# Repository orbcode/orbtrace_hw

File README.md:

ORBTrace Hardware
=================

This is the repository for various hardware for the ORBTrace project. There are various bits and pieces here but the most important ones are;

* ORBTrace Mini V1.0
* ORBMule demo board
* Breakout board for PMOD

You can also find the openSCAD source materials, and vinyl graphics, for the ORBTrace Mini V1 case.

These materials are provided in open form to learn from and improve on. We have deliberately chosen to not provide Gerbers for ORBTrace mini or STLs for the caseworks since your manufacturing processes are likely different to ours. Drop a note if you need those.

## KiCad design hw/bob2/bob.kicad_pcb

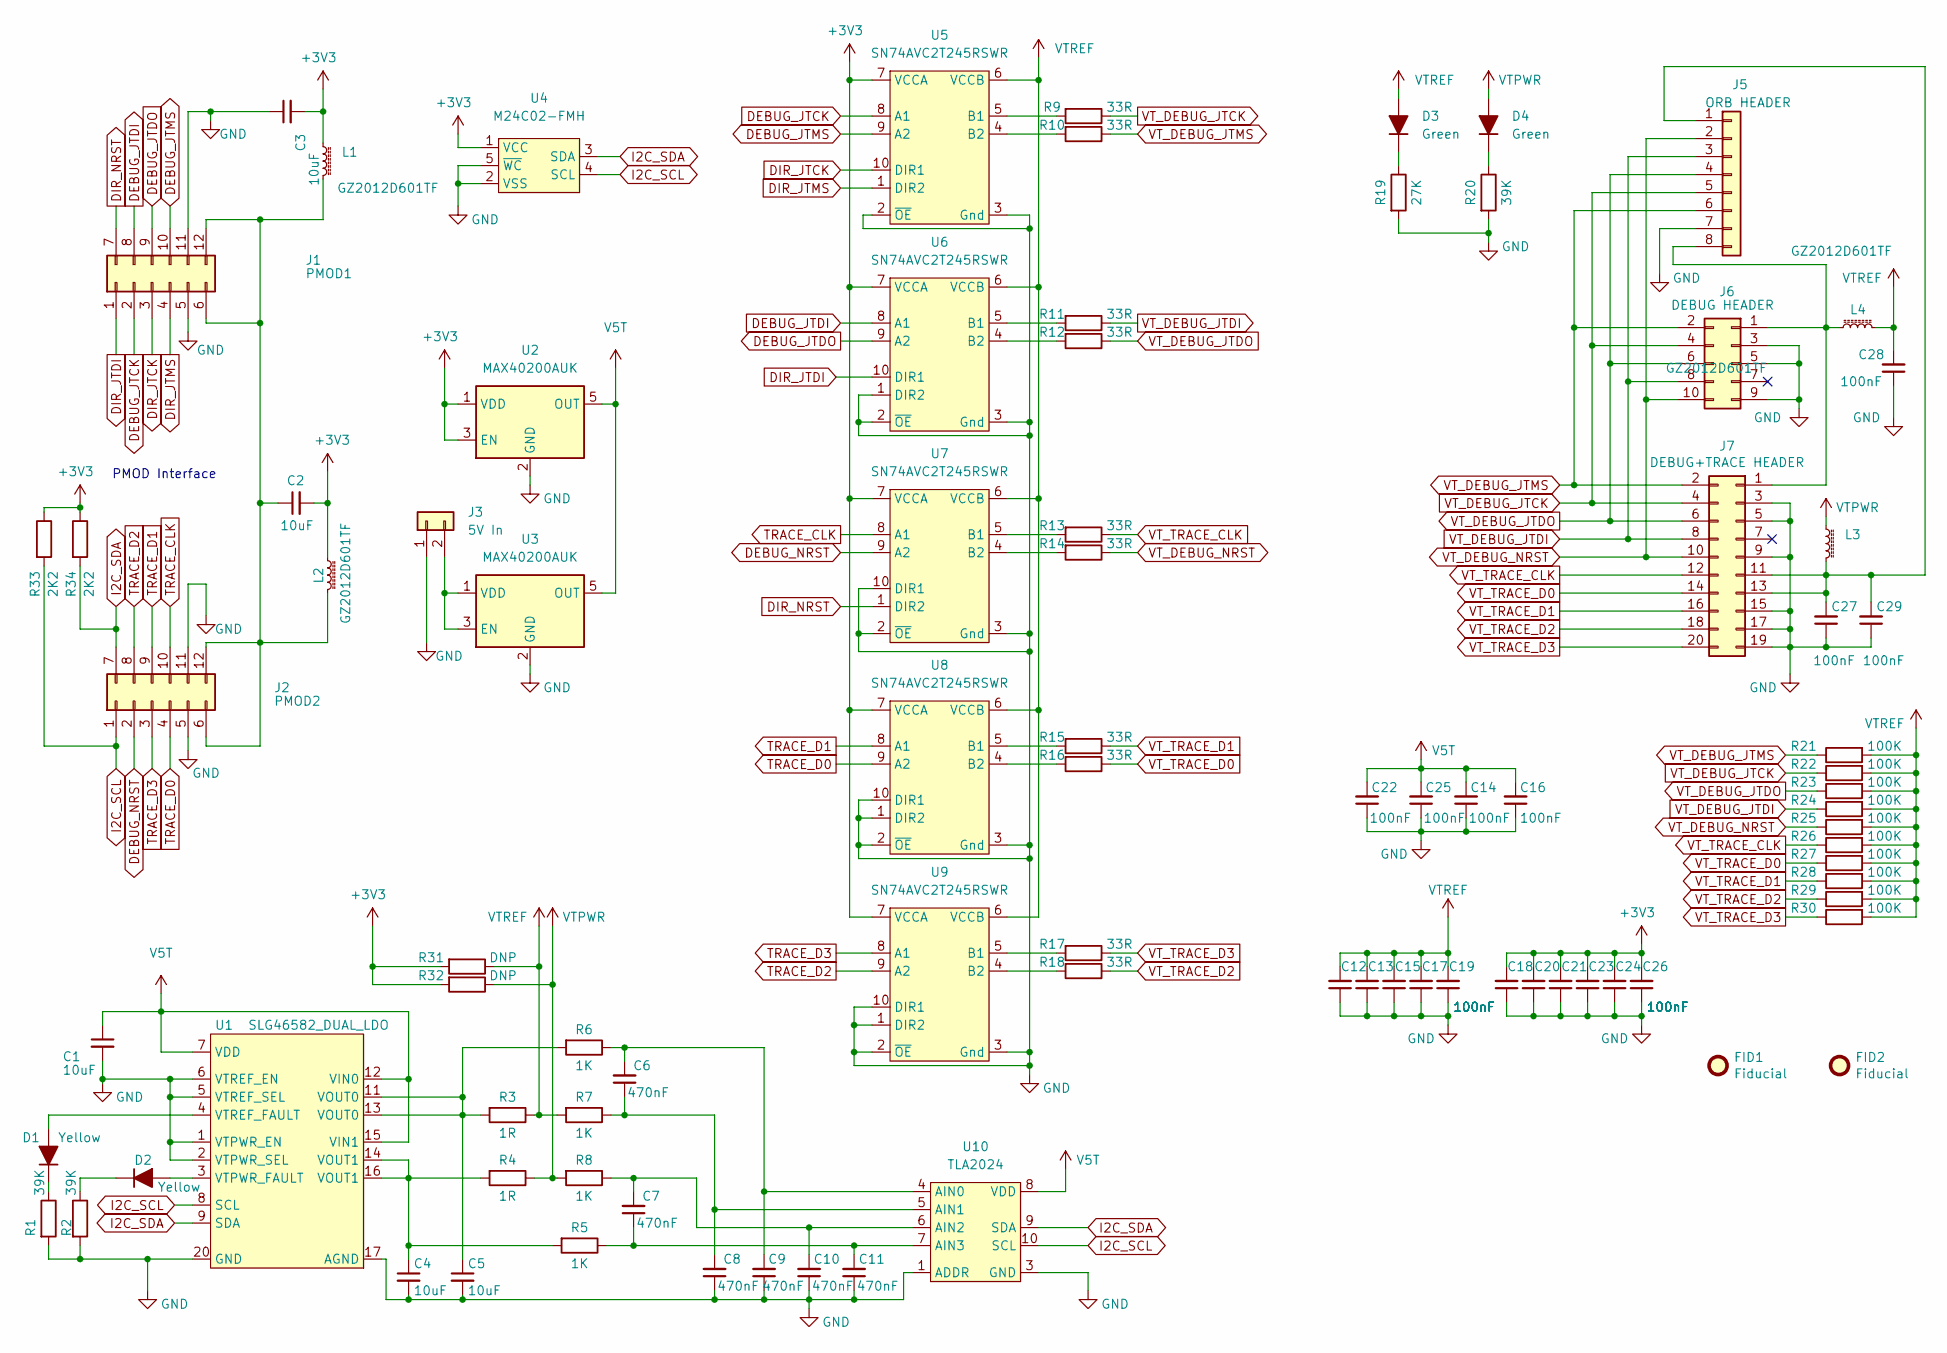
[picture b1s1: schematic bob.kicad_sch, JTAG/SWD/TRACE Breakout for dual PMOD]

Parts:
C1, C2, C3, C4, C5: 10uF; C_0603_1608Metric; JLC CODE C19702
C6, C7, C8, C9, C10, C11: 470nF; C_0402_1005Metric; JLC CODE C47339
C12, C13, C14, C15, C16, C17, C18, C19, C20, C21, C22, C23, C24, C25, C26, C27, C28, C29: 100nF; C_0402_1005Metric; JLC CODE C307331
D1, D2: Yellow; LED_0603_1608Metric; JLC CODE C72038
D3, D4: Green; LED_0603_1608Metric; JLC CODE C72043
FID1, FID2: Fiducial; Fiducial_0.75mm_Mask1.5mm
J1: PMOD1; pmod_pin_array_6x2
J2: PMOD2; pmod_pin_array_6x2
J3: 5V In; PinHeader_1x02_P2.54mm_Vertical
J5: ORB HEADER; PinHeader_1x08_P2.54mm_Vertical
J6: DEBUG HEADER; PinHeader_2x05_P1.27mm_Vertical_SMD
J7: DEBUG+TRACE HEADER; PinHeader_2x10_P1.27mm_Vertical_SMD
L1, L2, L3, L4: GZ2012D601TF; L_0805_2012Metric; JLC CODE C1017
R1, R2, R20: 39K; R_0402_1005Metric; JLC CODE C25783
R3, R4: 1R; R_0603_1608Metric; JLC CODE C22936
R5, R6, R7, R8: 1K; R_0402_1005Metric; JLC CODE C21190
R9, R10, R11, R12, R13, R14, R15, R16, R17, R18: 33R; R_0603_1608Metric; JLC CODE C23140
R19: 27K; R_0402_1005Metric; JLC CODE C25771
R21, R22, R23, R24, R25, R26, R27, R28, R29, R30: 100K; R_0402_1005Metric; JLC CODE C22936
R31, R32: DNP; R_0603_1608Metric
R33, R34: 2K2; R_0402_1005Metric; JLC CODE C4190
U1: SLG46582_DUAL_LDO; STQFN-20
U2, U3: MAX40200AUK; SOT-23-5; JLC CODE C2649430
U4: M24C02-FMH; DFN-5; JLC CODE C222197
U5, U6, U7, U8, U9: SN74AVC2T245RSWR; UQFN-10; JLC CODE C128418
U10: TLA2024; PQFP-N10; JLC CODE C2876104

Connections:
+3V3: C2.2, C3.2, C18.2, C20.2, C21.2, C23.2, C24.2, C26.2, L1.1, L2.1, R31.2, R32.2, R33.1, R34.1, U2.1 (VDD), U2.3 (EN), U4.1 (VCC), U5.7 (VCCA), U6.7 (VCCA), U7.7 (VCCA), U8.7 (VCCA), U9.7 (VCCA)
DEBUG_JTCK: J1.2, U5.8 (A1)
DEBUG_JTDI: J1.8, U6.8 (A1)
DEBUG_JTDO: J1.9, U6.9 (A2)
DEBUG_JTMS: J1.10, U5.9 (A2)
DEBUG_NRST: J2.2, U7.9 (A2)
DIR_JTCK: J1.3, U5.10 (DIR1)
DIR_JTDI: J1.1, U6.10 (DIR1)
DIR_JTMS: J1.4, U5.1 (DIR2)
DIR_NRST: J1.7, U7.1 (DIR2)
GND: C1.2, C3.1, C4.2, C5.2, C8.1, C9.1, C10.1, C11.1, C12.1, C13.1, C14.1, C15.1, C16.1, C17.1, C18.1, C19.1, C20.1, C21.1, C22.1, C23.1, C24.1, C25.1, C26.1, C27.1, C28.1, C29.1, J1.5, J1.11, J2.5, J2.11, J3.1, J5.7, J6.3, J6.5, J6.9, J7.3, J7.5, J7.9, J7.15, J7.17, J7.19, R1.2, R2.2, R19.2, R20.2, U1.1 (VTPWR_EN), U1.2 (VTPWR_SEL), U1.5 (VTREF_SEL), U1.6 (VTREF_EN), U1.17 (AGND), U1.20 (GND), U2.2 (GND), U3.2 (GND), U4.2 (VSS), U4.5 (~WC), U5.2 (~OE), U5.3 (Gnd), U6.1 (DIR2), U6.2 (~OE), U6.3 (Gnd), U7.2 (~OE), U7.3 (Gnd), U7.10 (DIR1), U8.1 (DIR2), U8.2 (~OE), U8.3 (Gnd), U8.10 (DIR1), U9.1 (DIR2), U9.2 (~OE), U9.3 (Gnd), U9.10 (DIR1), U10.1 (ADDR), U10.3 (GND)
I2C_SCL: J2.1, R33.2, U1.8 (SCL), U4.4 (SCL), U10.10 (SCL)
I2C_SDA: J2.7, R34.2, U1.9 (SDA), U4.3 (SDA), U10.9 (SDA)
unnamed: C2.1, J1.6, J1.12, J2.6, J2.12, L1.2, L2.2
unnamed: C4.1, R4.2, R5.2, U1.14 (VOUT1), U1.16 (VOUT1)
unnamed: C5.1, R3.2, R6.2, U1.11 (VOUT0), U1.13 (VOUT0)
unnamed: C6.1, C8.2, R7.1, U10.5 (AIN1)
unnamed: C6.2, C9.2, R6.1, U10.4 (AIN0)
unnamed: C7.2, C10.2, R8.1, U10.6 (AIN2)
unnamed: C7.1, C11.2, R5.1, U10.7 (AIN3)
unnamed: C27.2, C29.2, J5.1, J7.11, J7.13, L3.2
unnamed: D1.1 (K), R1.1
unnamed: D1.2 (A), U1.4 (VTREF_FAULT)
unnamed: D2.1 (K), R2.1
unnamed: D2.2 (A), U1.3 (VTPWR_FAULT)
unnamed: D3.1 (K), R19.1
unnamed: D4.1 (K), R20.1
unnamed: J3.2, U3.1 (VDD), U3.3 (EN)
unnamed: J5.8, J6.1, J7.1, L4.1
unnamed: R9.2, U5.5 (B1)
unnamed: R10.2, U5.4 (B2)
unnamed: R11.2, U6.5 (B1)
unnamed: R12.2, U6.4 (B2)
unnamed: R13.2, U7.5 (B1)
unnamed: R14.2, U7.4 (B2)
unnamed: R15.2, U8.5 (B1)
unnamed: R16.2, U8.4 (B2)
unnamed: R17.2, U9.5 (B1)
unnamed: R18.2, U9.4 (B2)
TRACE_CLK: J2.10, U7.8 (A1)
TRACE_D0: J2.4, U8.9 (A2)
TRACE_D1: J2.9, U8.8 (A1)
TRACE_D2: J2.8, U9.9 (A2)
TRACE_D3: J2.3, U9.8 (A1)
V5T: C1.1, C14.2, C16.2, C22.2, C25.2, U1.7 (VDD), U1.12 (VIN0), U1.15 (VIN1), U2.5 (OUT), U3.5 (OUT), U10.8 (VDD)
VTPWR: D4.2 (A), L3.1, R4.1, R8.2, R32.1
VTREF: C12.2, C13.2, C15.2, C17.2, C19.2, C28.2, D3.2 (A), L4.2, R3.1, R7.2, R21.2, R22.2, R23.2, R24.2, R25.2, R26.2, R27.2, R28.2, R29.2, R30.2, R31.1, U5.6 (VCCB), U6.6 (VCCB), U7.6 (VCCB), U8.6 (VCCB), U9.6 (VCCB)
VT_DEBUG_JTCK: J5.5, J6.4, J7.4, R9.1, R22.1
VT_DEBUG_JTDI: J5.3, J6.8, J7.8, R11.1, R24.1
VT_DEBUG_JTDO: J5.4, J6.6, J7.6, R12.1, R23.1
VT_DEBUG_JTMS: J5.6, J6.2, J7.2, R10.1, R21.1
VT_DEBUG_NRST: J5.2, J6.10, J7.10, R14.1, R25.1
VT_TRACE_CLK: J7.12, R13.1, R26.1
VT_TRACE_D0: J7.14, R16.1, R27.1
VT_TRACE_D1: J7.16, R15.1, R28.1
VT_TRACE_D2: J7.18, R18.1, R29.1
VT_TRACE_D3: J7.20, R17.1, R30.1

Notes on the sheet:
PMOD Interface

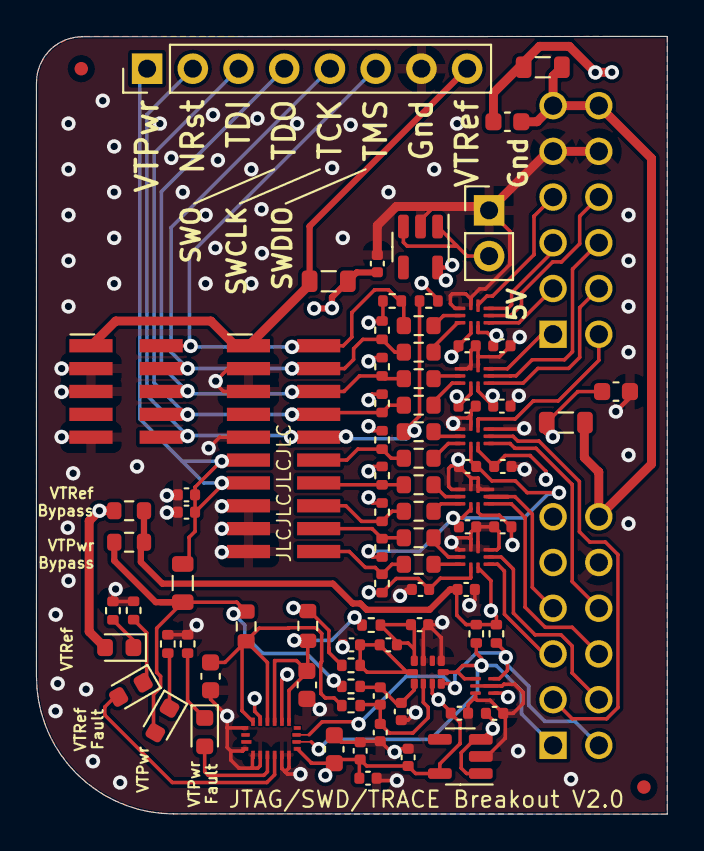
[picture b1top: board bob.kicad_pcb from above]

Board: 4 copper layers, 35.0 x 43.2 mm, 89 parts (0 on the bottom side), 57 nets.

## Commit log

2021-09-10 Transfer of files from orbtrace repository
2022-05-23 Tidying up and adding missing files
2022-09-05 generate case bottom STL files
    - case bottom
    - case bottom with logo
2022-11-01 Addition of v2 breakout board for dual pmod
2023-06-27 Addition of STM32F730 mule board circuit diagram
2023-10-11 orbtrace_mini: Add greenpak configurations.
